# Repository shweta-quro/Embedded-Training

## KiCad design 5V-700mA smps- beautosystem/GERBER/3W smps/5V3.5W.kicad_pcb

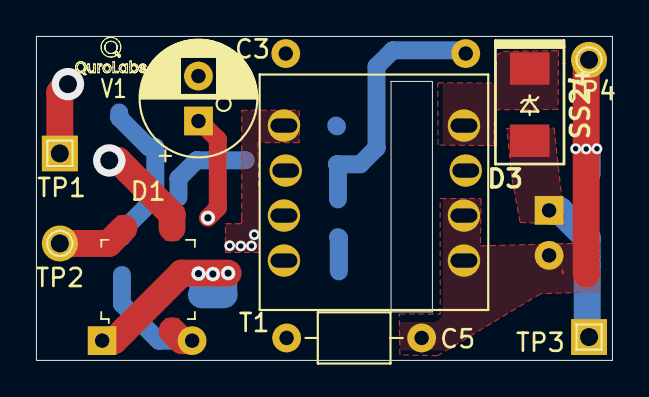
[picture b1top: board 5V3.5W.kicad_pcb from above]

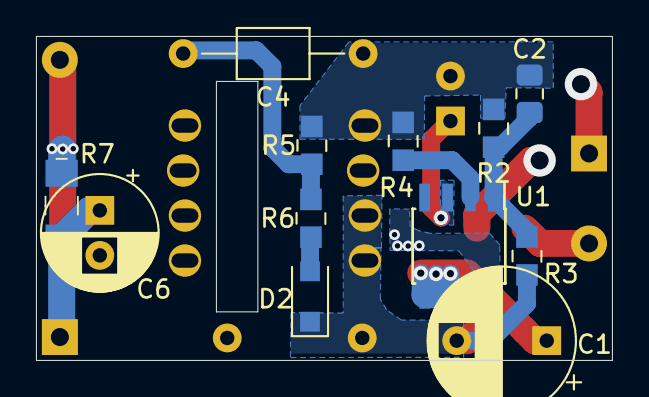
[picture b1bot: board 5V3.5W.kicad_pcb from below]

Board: 2 copper layers, 32.0 x 18.0 mm, 21 parts (12 on the bottom side), 12 nets.

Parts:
C1: 4.7uF/400V; CP_Radial_D8.0mm_P5.00mm
C2: DNA; C_0805_2012Metric_Pad1.18x1.45mm_HandSolder
C3: 22uF/50V; CP_Radial_D6.3mm_P2.50mm
C4: 2G103J; C_Axial_L3.8mm_D2.6mm_P10.00mm_Horizontal
C5: 222M/400V; C_Axial_L3.8mm_D2.6mm_P7.50mm_Horizontal
C6: 470uF/10V; CP_Radial_D6.3mm_P2.50mm
D1: MB6S; TO-269AA
D2: F7; D_SOD-123F
D3: SS24; D_SS14
R2: 4.99K; 0805
R3: 150K; 0805
R4: 1R; 0805
R5: 75K; 0805
R6: 47R; 0805
R7: 470R; 1206
T1: EE13-H
TP1, TP3: TestPoint; TestPoint_THTPad_1.0x1.0mm_Drill0.5mm
TP2, TP4: TestPoint; TestPoint_THTPad_D1.0mm_Drill0.5mm
U1: DK935; SOIC-8-N7_3.9x4.9mm_P1.27mm

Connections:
unnamed: C1.1, D1.1, U1.5, U1.6
unnamed: C1.2, C5.2, D1.2, D2.1, R3.1, T1.3, T1.4
unnamed: C2.1, R2.1, R3.2, U1.1
unnamed: C2.2, C3.2, C4.1, R2.2, R4.1, R5.2, T1.1, U1.8
unnamed: C3.1, U1.3
unnamed: C4.2, R5.1, R6.2
unnamed: C5.1, C6.2, R7.2, T1.5, T1.6, TP4.1
unnamed: C6.1, D3.1, R7.1, TP3.1
unnamed: D1.4, TP2.1
unnamed: D2.2, R6.1
unnamed: D3.2, T1.8
unnamed: R4.2, U1.2

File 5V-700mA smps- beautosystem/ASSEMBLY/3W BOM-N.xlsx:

null | References | Value | Footprint | Quantity
1 | C1 | 4.7uF/400V | CP_Radial_D8.0mm_P5.00mm | 1
2 | C2 | DNA | C_0805_2012Metric_Pad1.18x1.45mm_HandSolder | 1
3 | C3 | 22uF/50V | CP_Radial_D6.3mm_P2.50mm | 1
4 | C4 | 2G103J | C_Axial_L3.8mm_D2.6mm_P10.00mm_Horizontal | 1
5 | C5 | 222M/400V | C_Axial_L3.8mm_D2.6mm_P7.50mm_Horizontal | 1
6 | C6 | 470uF/10V | CP_Radial_D6.3mm_P2.50mm | 1
7 | R2 | 4.99K | 805 | 1
8 | R3 | 150K | 805 | 1
9 | R4 | 1R | 805 | 1
10 | R5 | 75K | 805 | 1
11 | R6 | 47R | 805 | 1
12 | R7 | 470R | 1206 | 1
13 | D1 | MB6S | TO-269AA | 1
14 | D2 | F7 | D_SOD-123F | 1
15 | D3 | SS24 | D_SS14 | 1
16 | U1 | DK935 | SOIC-8-N7_3.9x4.9mm_P1.27mm | 1
17 | T1 | EE13-H | EE13-H | 1
18 | R1 |  | FUSE | 1
19 | TP1,TP2,TP3,TP4 |  | 0.5drill, 1mm

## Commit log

2022-09-12 upload project
